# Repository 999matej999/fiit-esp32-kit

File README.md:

# FIIT ESP32 Kit
Board contains these components:
* 4x Buttons (needs internal pull-up resistor)
* 4x LED (red, yellow, green, blue)
* Programmable RGB LED
* Temperature & Humidity I<sup>2</sup>C Sensor AHT20
* Analog Light Sensor SFH320
* 2x QWIIC I<sup>2</sup>C connectors

For uploading code use USB UART by default.

## Pinout

GPIOX represents the pin marking, where X is the pin number that needs to be used in the Arduino IDE.

Please consider proper electrical connection to prevent electrical shortcuts.

## Arduino IDE
First of all ensure you have Arduino IDE and [ESP32 boards](https://randomnerdtutorials.com/installing-the-esp32-board-in-arduino-ide-windows-instructions/) properly installed.
Select board: ESP32S3 Dev Module
For basic examples use default configuration.

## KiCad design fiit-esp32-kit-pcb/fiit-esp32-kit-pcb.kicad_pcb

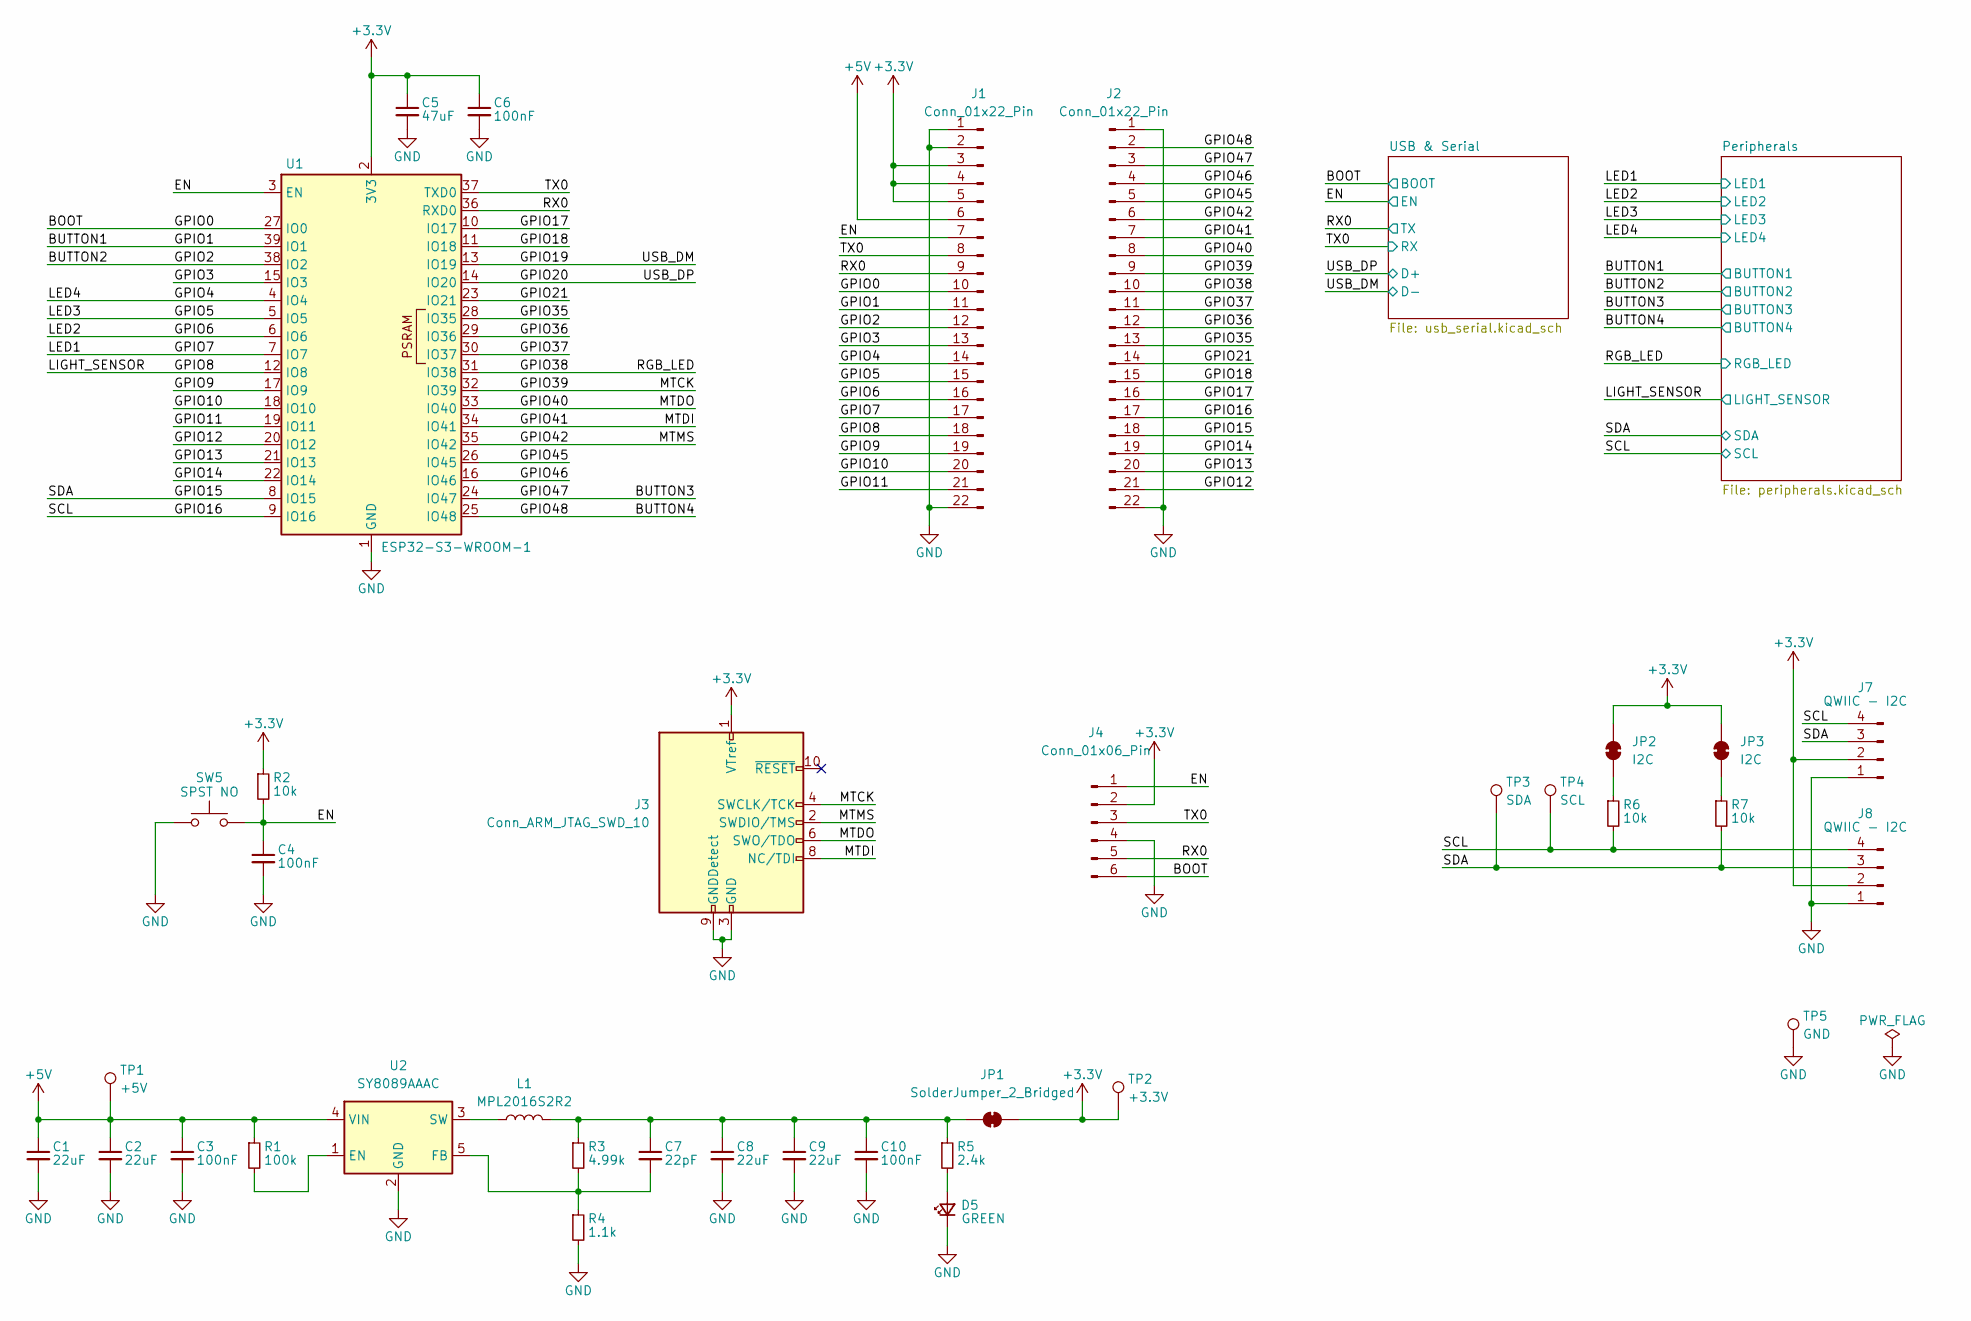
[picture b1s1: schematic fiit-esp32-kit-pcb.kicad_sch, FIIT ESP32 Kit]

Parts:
C1, C2, C8, C9: 22uF; C_0603_1608Metric; Manufacturer Part Number CL10A226MQ8NRNC; LCSC C59461
C3, C4, C6, C10: 100nF; C_0603_1608Metric; Manufacturer Part Number CC0603KRX7R9BB104; LCSC C14663
C5: 47uF; C_0805_2012Metric; Manufacturer Part Number CL21A476MQYNNNE; LCSC C16780
C7: 22pF; C_0603_1608Metric; Manufacturer Part Number CL10C220JB8NNNC; LCSC C1653
D5: GREEN; LED_0805_2012Metric; Manufacturer Part Number KT-0805G; LCSC C2297
J1, J2: Conn_01x22_Pin; PinHeader_1x22_P2.54mm_Vertical; Manufacturer Part Number DS1021-1x22SF11-B; LCSC C7430378
J3: Conn_ARM_JTAG_SWD_10; PinHeader_2x05_P1.27mm_Vertical_SMD
J4: Conn_01x06_Pin; PinHeader_2x03_P1.27mm_Vertical_SMD
J7, J8: QWIIC - I2C; JST_SH_SM04B-SRSS-TB_1x04-1MP_P1.00mm_Horizontal; Manufacturer Part Number SM04B-SRSS-TB(LF)(SN); LCSC C160404
JP1: SolderJumper_2_Bridged; SolderJumper-2_P1.3mm_Bridged_RoundedPad1.0x1.5mm
JP2, JP3: I2C; SolderJumper-2_P1.3mm_Bridged_RoundedPad1.0x1.5mm
L1: MPL2016S2R2; INDC2116X100N; Manufacturer Part Number MPL2016S2R2MHT; LCSC C42215
R1: 100k; R_0603_1608Metric; Manufacturer Part Number 0603WAF1003T5E; LCSC C25803
R2, R6, R7: 10k; R_0603_1608Metric; Manufacturer Part Number 0603WAF1002T5E; LCSC C25804
R3: 4.99k; R_0603_1608Metric; Manufacturer Part Number 0603WAF4991T5E; LCSC C23046
R4: 1.1k; R_0603_1608Metric; Manufacturer Part Number 0603WAF1101T5E; LCSC C22764
R5: 2.4k; R_0603_1608Metric; Manufacturer Part Number 0603WAF2401T5E; LCSC C22940
SW5: SPST NO; SW_SPST_PTS647_Sx38; Manufacturer Part Number TS-1187A-B-A-B; LCSC C318884
TP1: +5V; TestPoint_Pad_D1.5mm
TP2: +3.3V; TestPoint_Pad_D1.5mm
TP3: SDA; TestPoint_Pad_D1.5mm
TP4: SCL; TestPoint_Pad_D1.5mm
TP5: GND; TestPoint_Pad_D1.5mm
U1: ESP32-S3-WROOM-1; Manufacturer Part Number ESP32-S3-WROOM-1-N16R2; LCSC C2913205
U2: SY8089AAAC; TSOT-23-5; Manufacturer Part Number SY8089AAAC; LCSC C78988

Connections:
+3.3V: C5.1, C6.1, J1.3, J1.4, J1.5, J3.1 (VTref), J4.2, J7.2, J8.2, JP1.2 (B), JP2.2 (B), JP3.2 (B), R2.1, TP2.1, U1.2 (3V3); also elsewhere on the board
+5V: C1.1, C2.1, C3.1, J1.6, R1.1, TP1.1, U2.4 (VIN); also elsewhere on the board
/BOOT: J1.10, J4.6, U1.27 (IO0); also elsewhere on the board
/BUTTON1: J1.11, U1.39 (IO1); also elsewhere on the board
/BUTTON2: J1.12, U1.38 (IO2); also elsewhere on the board
/BUTTON3: J2.3, U1.24 (IO47); also elsewhere on the board
/BUTTON4: J2.2, U1.25 (IO48); also elsewhere on the board
/EN: C4.1, J1.7, J4.1, R2.2, SW5.2, U1.3 (EN); also elsewhere on the board
/GPIO3: J1.13, U1.15 (IO3)
/GPIO4: J1.14, U1.4 (IO4); also elsewhere on the board
/GPIO5: J1.15, U1.5 (IO5); also elsewhere on the board
/GPIO6: J1.16, U1.6 (IO6); also elsewhere on the board
/GPIO7: J1.17, U1.7 (IO7); also elsewhere on the board
/GPIO8: J1.18, U1.12 (IO8); also elsewhere on the board
/GPIO9: J1.19, U1.17 (IO9)
/GPIO10: J1.20, U1.18 (IO10)
/GPIO11: J1.21, U1.19 (IO11)
/GPIO12: J2.21, U1.20 (IO12)
/GPIO13: J2.20, U1.21 (IO13)
/GPIO14: J2.19, U1.22 (IO14)
/GPIO15: J2.18, J7.3, J8.3, R7.2, TP3.1, U1.8 (IO15); also elsewhere on the board
/GPIO16: J2.17, J7.4, J8.4, R6.2, TP4.1, U1.9 (IO16); also elsewhere on the board
/GPIO17: J2.16, U1.10 (IO17)
/GPIO18: J2.15, U1.11 (IO18)
/GPIO19: U1.13 (IO19); also elsewhere on the board
/GPIO20: U1.14 (IO20); also elsewhere on the board
/GPIO21: J2.14, U1.23 (IO21)
/GPIO35: J2.13, U1.28 (IO35)
/GPIO36: J2.12, U1.29 (IO36)
/GPIO37: J2.11, U1.30 (IO37)
/GPIO38: J2.10, U1.31 (IO38); also elsewhere on the board
/GPIO39: J2.9, J3.4 (SWCLK/TCK), U1.32 (IO39)
/GPIO40: J2.8, J3.6 (SWO/TDO), U1.33 (IO40)
/GPIO41: J2.7, J3.8 (NC/TDI), U1.34 (IO41)
/GPIO42: J2.6, J3.2 (SWDIO/TMS), U1.35 (IO42)
/GPIO45: J2.5, U1.26 (IO45)
/GPIO46: J2.4, U1.16 (IO46)
/RX0: J1.9, J4.5, U1.36 (RXD0); also elsewhere on the board
/TX0: J1.8, J4.3, U1.37 (TXD0); also elsewhere on the board
GND: C1.2, C2.2, C3.2, C4.2, C5.2, C6.2, C8.2, C9.2, C10.2, D5.1 (K), J1.1, J1.2, J1.22, J2.1, J2.22, J3.3 (GND), J3.5 (GND), J3.9 (GNDDetect), J4.4, J7.1, J8.1, R4.2, SW5.1, TP5.1, U1.1 (GND), U1.40 (GND), U1.41 (GND), U2.2 (GND); also elsewhere on the board
unnamed: D5.2 (A), R5.2
unnamed: C7.1, C8.1, C9.1, C10.1, JP1.1 (A), L1.2, R3.1, R5.1
unnamed: JP2.1 (A), R6.1
unnamed: JP3.1 (A), R7.1
unnamed: R1.2, U2.1 (EN)
unnamed: C7.2, R3.2, R4.1, U2.5 (FB)
unnamed: L1.1, U2.3 (SW)

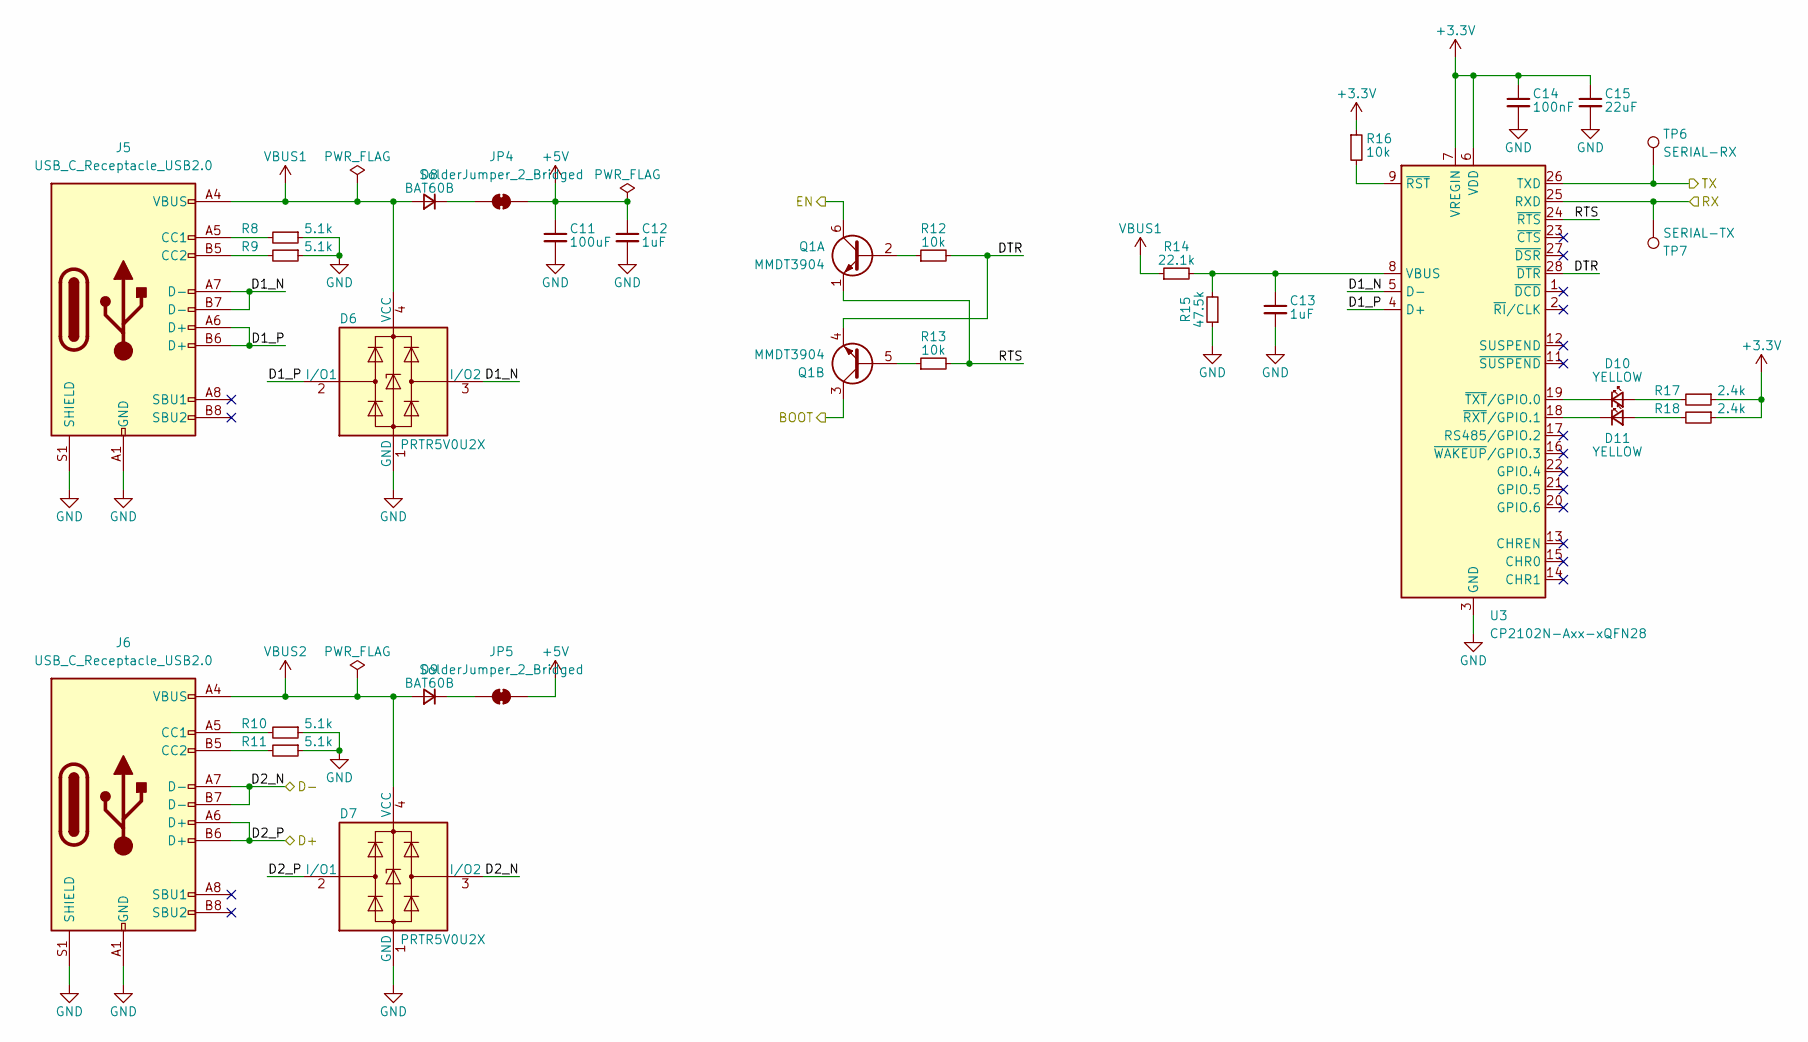
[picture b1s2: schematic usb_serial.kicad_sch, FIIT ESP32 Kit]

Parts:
C11: 100uF; C_1206_3216Metric; Manufacturer Part Number CL31A107MQHNNNE; LCSC C15008
C12, C13: 1uF; C_0603_1608Metric; Manufacturer Part Number CL10A105KB8NNNC; LCSC C15849
C14: 100nF; C_0603_1608Metric; Manufacturer Part Number CC0603KRX7R9BB104; LCSC C14663
C15: 22uF; C_0603_1608Metric; Manufacturer Part Number CL10A226MQ8NRNC; LCSC C59461
D6, D7: PRTR5V0U2X; SOT-143; Manufacturer Part Number PRTR5V0U2X-HXY; LCSC C5337179
D8, D9: BAT60B; D_SOD-323; Manufacturer Part Number BAT60B; LCSC C3018529
D10, D11: YELLOW; LED_0805_2012Metric; Manufacturer Part Number KT-0805Y; LCSC C2296
J5, J6: USB_C_Receptacle_USB2.0; USB_C_Receptacle_G-Switch_GT-USB-7010ASV; Manufacturer Part Number USB-TYPE-C-018; LCSC C2927038
JP4, JP5: SolderJumper_2_Bridged; SolderJumper-2_P1.3mm_Bridged_RoundedPad1.0x1.5mm
Q1: MMDT3904; SOT-363_SC-70-6; Manufacturer Part Number MMDT3904; LCSC C3018510
R8, R9, R10, R11: 5.1k; R_0603_1608Metric; Manufacturer Part Number 0603WAF5101T5E; LCSC C23186
R12, R13, R16: 10k; R_0603_1608Metric; Manufacturer Part Number 0603WAF1002T5E; LCSC C25804
R14: 22.1k; R_0603_1608Metric; Manufacturer Part Number 0603WAF2212T5E; LCSC C25961
R15: 47.5k; R_0603_1608Metric; Manufacturer Part Number 0603WAF4752T5E; LCSC C23061
R17, R18: 2.4k; R_0603_1608Metric; Manufacturer Part Number 0603WAF2401T5E; LCSC C22940
TP6: SERIAL-RX; TestPoint_Pad_D1.5mm
TP7: SERIAL-TX; TestPoint_Pad_D1.5mm
U3: CP2102N-Axx-xQFN28; QFN-28-1EP_5x5mm_P0.5mm_EP3.35x3.35mm; Manufacturer Part Number CP2102N-A02-GQFN28R; LCSC C964632

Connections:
+3.3V: C14.1, C15.1, R16.1, R17.1, R18.1, U3.6 (VDD), U3.7 (VREGIN); also elsewhere on the board
+5V: C11.1, C12.1, JP4.2 (B), JP5.2 (B); also elsewhere on the board
/BOOT: Q1.3 (C2); also elsewhere on the board
/EN: Q1.6 (C1); also elsewhere on the board
/GPIO19: D7.3 (I/O2), J6.A7 (D-), J6.B7 (D-); also elsewhere on the board
/GPIO20: D7.2 (I/O1), J6.A6 (D+), J6.B6 (D+); also elsewhere on the board
/RX0: TP6.1, U3.26 (TXD); also elsewhere on the board
/TX0: TP7.1, U3.25 (RXD); also elsewhere on the board
/USB & Serial/D1_N: D6.3 (I/O2), J5.A7 (D-), J5.B7 (D-), U3.5 (D-)
/USB & Serial/D1_P: D6.2 (I/O1), J5.A6 (D+), J5.B6 (D+), U3.4 (D+)
/USB & Serial/DTR: Q1.4 (E2), R12.2, U3.28 (~DTR)
/USB & Serial/RTS: Q1.1 (E1), R13.2, U3.24 (~RTS)
GND: C11.2, C12.2, C13.2, C14.2, C15.2, D6.1 (GND), D7.1 (GND), J5.A1 (GND), J5.A12 (GND), J5.B1 (GND), J5.B12 (GND), J5.S1 (SHIELD), J6.A1 (GND), J6.A12 (GND), J6.B1 (GND), J6.B12 (GND), J6.S1 (SHIELD), R8.1, R9.1, R10.1, R11.1, R15.1, U3.3 (GND), U3.29 (GND); also elsewhere on the board
unnamed: D8.1 (K), JP4.1 (A)
unnamed: D9.1 (K), JP5.1 (A)
unnamed: D10.2 (A), R17.2
unnamed: D10.1 (K), U3.19 (~TXT/GPIO.0)
unnamed: D11.2 (A), R18.2
unnamed: D11.1 (K), U3.18 (~RXT/GPIO.1)
unnamed: J5.A5 (CC1), R8.2
unnamed: J5.B5 (CC2), R9.2
unnamed: J6.A5 (CC1), R10.2
unnamed: J6.B5 (CC2), R11.2
unnamed: Q1.2 (B1), R12.1
unnamed: Q1.5 (B2), R13.1
unnamed: C13.1, R14.2, R15.2, U3.8 (VBUS)
unnamed: R16.2, U3.9 (~RST)
VBUS1: D6.4 (VCC), D8.2 (A), J5.A4 (VBUS), J5.A9 (VBUS), J5.B4 (VBUS), J5.B9 (VBUS), R14.1
VBUS2: D7.4 (VCC), D9.2 (A), J6.A4 (VBUS), J6.A9 (VBUS), J6.B4 (VBUS), J6.B9 (VBUS)

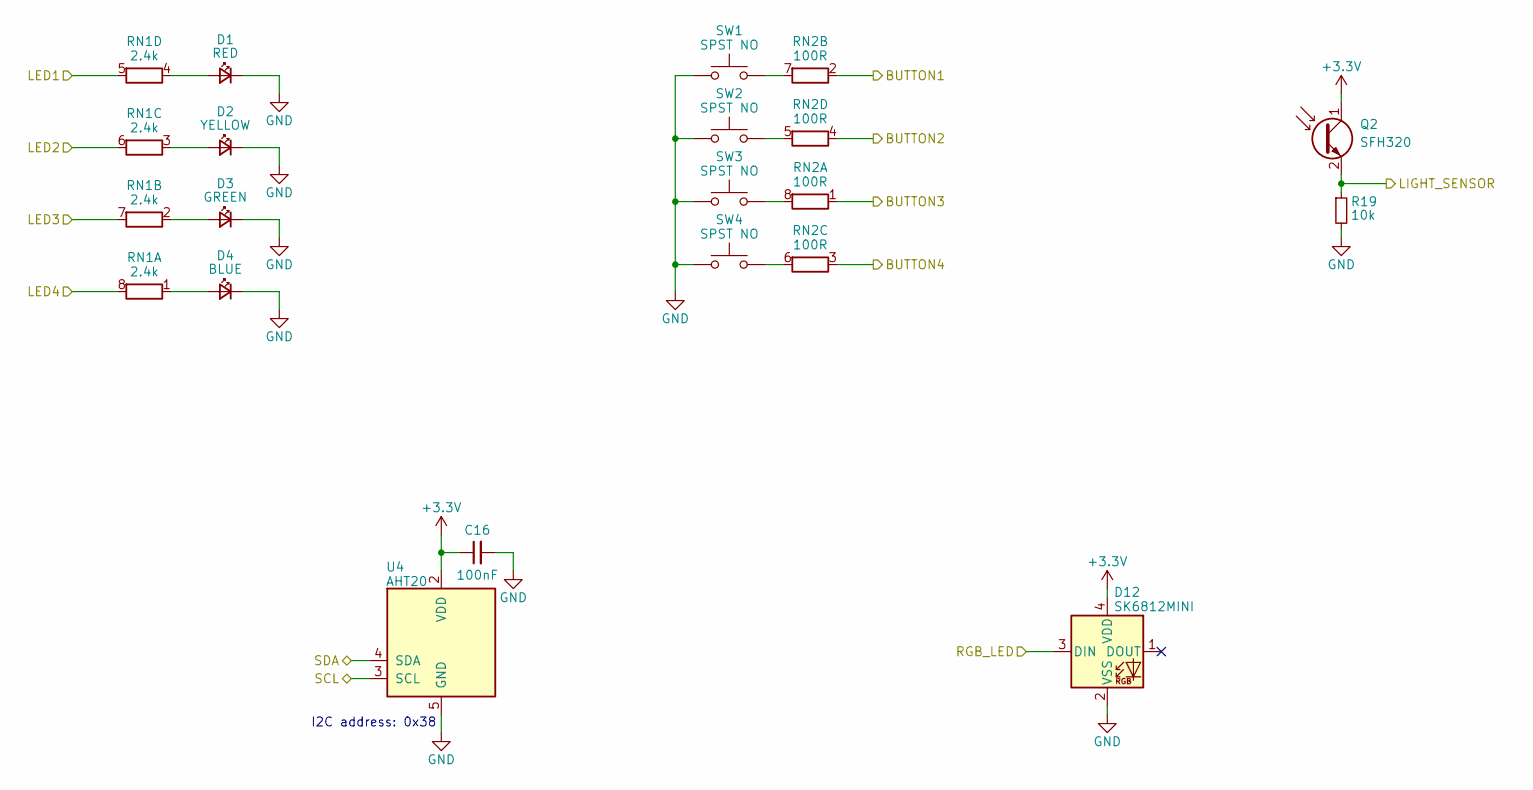
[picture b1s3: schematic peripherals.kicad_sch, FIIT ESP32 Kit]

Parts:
C16: 100nF; C_0603_1608Metric; Manufacturer Part Number CC0603KRX7R9BB104; LCSC C14663
D1: RED; LED_0805_2012Metric; Manufacturer Part Number KT-0805R; LCSC C2295
D2: YELLOW; LED_0805_2012Metric; Manufacturer Part Number KT-0805Y; LCSC C2296
D3: GREEN; LED_0805_2012Metric; Manufacturer Part Number KT-0805G; LCSC C2297
D4: BLUE; LED_0805_2012Metric; Manufacturer Part Number KT-0805B; LCSC C2293
D12: SK6812MINI; LED_SK6812MINI_PLCC4_3.5x3.5mm_P1.75mm; Manufacturer Part Number SK6812mini; LCSC C2886570
Q2: SFH320; TEMT6000X01; Manufacturer Part Number TEMT6000X01; LCSC C94098
R19: 10k; R_0603_1608Metric; Manufacturer Part Number 0603WAF1002T5E; LCSC C25804
RN1: 2.4k; R_Array_Convex_4x0603; Manufacturer Part Number 4D03WGF2401T5E; LCSC C425225
RN2: 100R; R_Array_Convex_4x0603; Manufacturer Part Number 4D03WGF1000T5E; LCSC C425240
SW1, SW2, SW3, SW4: SPST NO; SW_SPST_PTS647_Sx38; Manufacturer Part Number TS-1187A-B-A-B; LCSC C318884
U4: AHT20; Manufacturer Part Number AHT20; LCSC C2757850

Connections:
+3.3V: C16.1, D12.4 (VDD), Q2.1 (C), U4.2 (VDD); also elsewhere on the board
/BUTTON1: RN2.2 (R2.1); also elsewhere on the board
/BUTTON2: RN2.4 (R4.1); also elsewhere on the board
/BUTTON3: RN2.1 (R1.1); also elsewhere on the board
/BUTTON4: RN2.3 (R3.1); also elsewhere on the board
/GPIO4: RN1.8 (R1.2); also elsewhere on the board
/GPIO5: RN1.7 (R2.2); also elsewhere on the board
/GPIO6: RN1.6 (R3.2); also elsewhere on the board
/GPIO7: RN1.5 (R4.2); also elsewhere on the board
/GPIO8: Q2.2 (E), R19.1; also elsewhere on the board
/GPIO15: U4.4 (SDA); also elsewhere on the board
/GPIO16: U4.3 (SCL); also elsewhere on the board
/GPIO38: D12.3 (DIN); also elsewhere on the board
GND: C16.2, D1.1 (K), D2.1 (K), D3.1 (K), D4.1 (K), D12.2 (VSS), R19.2, SW1.1, SW2.1, SW3.1, SW4.1, U4.5 (GND); also elsewhere on the board
unnamed: D1.2 (A), RN1.4 (R4.1)
unnamed: D2.2 (A), RN1.3 (R3.1)
unnamed: D3.2 (A), RN1.2 (R2.1)
unnamed: D4.2 (A), RN1.1 (R1.1)
unnamed: RN2.8 (R1.2), SW3.2
unnamed: RN2.7 (R2.2), SW1.2
unnamed: RN2.6 (R3.2), SW4.2
unnamed: RN2.5 (R4.2), SW2.2

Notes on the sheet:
I2C address: 0x38

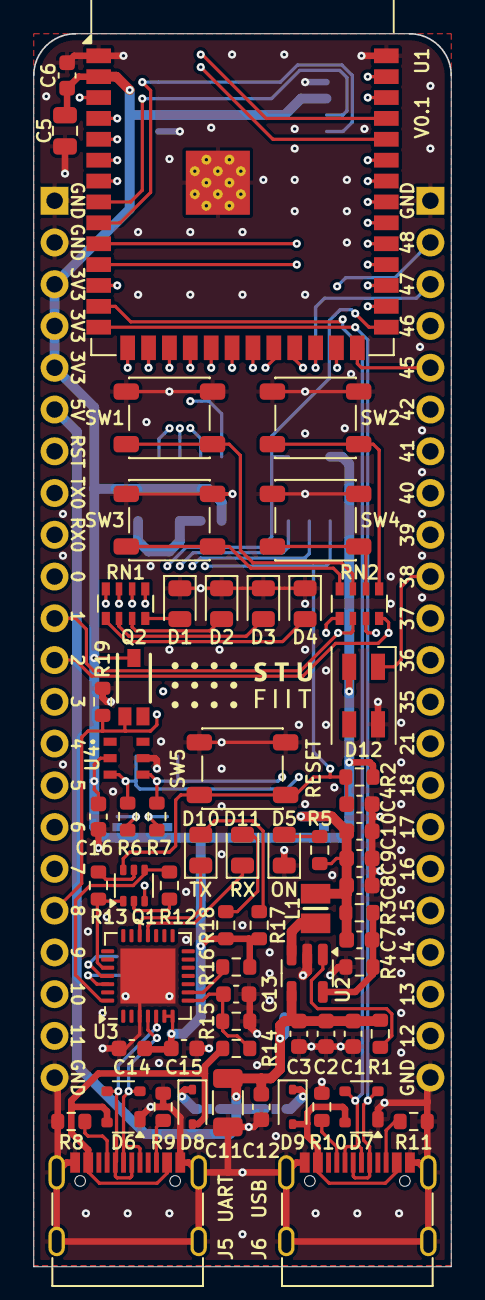
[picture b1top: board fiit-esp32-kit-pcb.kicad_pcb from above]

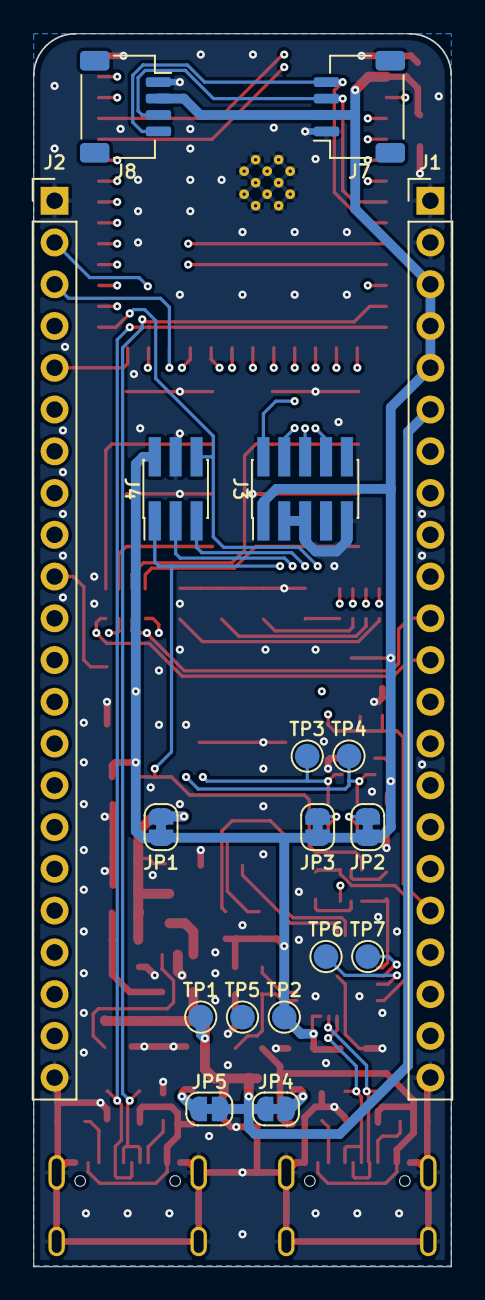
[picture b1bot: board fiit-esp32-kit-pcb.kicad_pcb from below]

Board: 4 copper layers, 25.4 x 75.0 mm, 81 parts (18 on the bottom side), 75 nets.

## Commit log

2024-07-21 added schematic drawing
2024-07-21 added footprint library
2024-07-21 footprints assignment
2024-07-21 updated manufacturer part numbers
2024-07-21 component placement
2024-07-30 updated components placement (unrouted 237)
2024-07-30 added some tracks (unrouted 76)
2024-07-30 added some tracks (unrouted 107)
2024-08-02 added some tracks (unrouted 0 !!!)
2024-08-04 final improvements
2024-08-04 added gerber files
2024-08-04 final changes
2024-08-04 added schematic
2024-09-18 added readme
2024-09-18 added basic examples
